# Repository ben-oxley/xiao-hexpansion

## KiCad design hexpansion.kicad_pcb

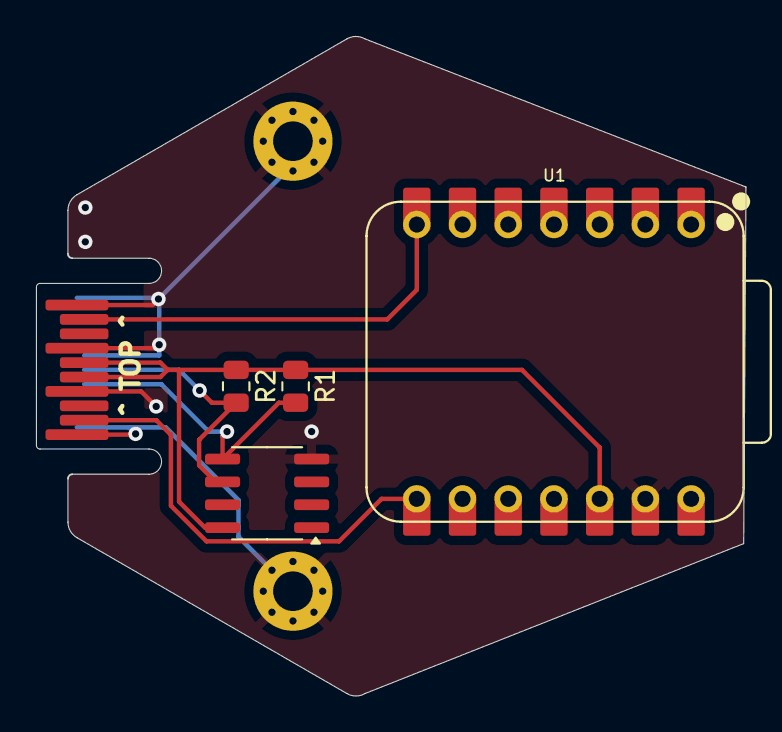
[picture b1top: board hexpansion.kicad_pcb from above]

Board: 2 copper layers, 39.4 x 36.6 mm, 7 parts (0 on the bottom side), 6 nets.

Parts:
H1, H2: MountingHole_Pad; MountingHole_2.2mm_M2_Pad_Via
J1: Hexpansion-Connector; hexpansion-edge-connector
R1, R2: R; R_0805_2012Metric
U1: XIAO-ESP32-S3-DIP
U2: FM24CL16B; SOIC-8_3.9x4.9mm_P1.27mm

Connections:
/3V3: J1.15 (3V3), J1.16 (3V3), R1.1, R2.1, U1.12 (3V3), U2.8 (VDD)
/GND: H1.1, H2.1, J1.1 (GND), J1.6 (HEXP_DET), J1.10 (GND), J1.11 (GND), J1.14 (GND), J1.17 (GND), J1.20 (GND), U1.13 (GND), U2.4 (VSS)
/HS_F: J1.12 (HS_F), U1.7 (PB08_A6_D6_TX)
/HS_I: J1.19 (HS_I), U1.8 (PB09_A7_D7_RX)
/SCL: J1.5 (SCL), R2.2, U2.6 (SCL)
/SDA: J1.4 (SDA), R1.2, U2.5 (SDA)
